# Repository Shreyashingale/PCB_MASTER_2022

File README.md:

# PCB_MASTER_2022
PCB files for robocon 2022

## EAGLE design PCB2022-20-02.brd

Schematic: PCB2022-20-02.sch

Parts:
3.3V_ARRAY: PINHD-1X5; 1X05
24V1, 24V2: AB_SCREW_TERMINAL_5MM_2PIN
BUZ-M: F/CM12P
BUZ-S: F/CM12P
C1, C2: C-EU025-025X050; C025-025X050
CYT-M: PINHD-1X3; 1X03
CYT-S: PINHD-1X3; 1X03
DEBUG-M: LED5MM
DEBUG-S: LED5MM
ENC-1, ENC-2: PINHD-1X4; 1X04
GNDARRAY: PINHD-1X5; 1X05
H2, H3, H4, H5, H6: MOUNT-HOLE3.2; 3,2
I2C-M1, I2C-M2, I2C-S1, I2C-S2: 4PIN_RELIMATE_CONNECTOR
LIM1, LIM2: AB_SCREW_TER_5MM_3PIN
LM358: DIL8; DIL08
M1, M2, M3, M5, M6: PINHD-1X8; 1X08
M4: PINHD-1X10; 1X10
M7: PINHD-2X18; 2X18
M-PL: D5-1A; SIL05A
M-SOLENOID1, M-SOLENOID2: AB_SCREW_TERMINAL_5MM_2PIN
M-SOLENOIDS: AB_SCREW_TER_5MM_3PIN
MASTER: ARDUINO_MEGA
NRF_SLAVE: PINHD-2X4; 2X04
ODRV-M1, ODRV-M2, ODRV-M3: 3PIN_RELIMATE_CONNECTOR
ODRV-S1, ODRV-S2, ODRV-S3: 3PIN_RELIMATE_CONNECTOR
P1, P2, P3, P4: AB_RIGHT_TER_BLK_3PIN
PARALLEL: SW_DIP-7; EDG-07
PPR-M: PINHD-1X3; 1X03
PPR-S: PINHD-1X3; 1X03
R1, R2, R3, R4: R-US_0204/5; 0204/5
RESET: DIP02YL
S1: PINHD-1X10; 1X10
S2, S3, S5, S6, S7: PINHD-1X8; 1X08
S4: PINHD-2X18; 2X18
S-CYT-PPR: 255SB
S-ENC-1, S-ENC-2: PINHD-1X4; 1X04
S-LIM1, S-LIM2: AB_SCREW_TER_5MM_3PIN
S-PL: D5-1A; SIL05A
S-SOLENOID1, S-SOLENOID2: AB_SCREW_TERMINAL_5MM_2PIN
S-SOLENOIDS: AB_SCREW_TER_5MM_3PIN
SABM1, SABM2, SABM3: PINHD-1X2; 1X02
SABS1, SABS2, SABS3: PINHD-1X2; 1X02
SERIAL: DIP02YL
SERVO-M: 3PIN_RELIMATE_CONNECTOR
SERVO-S: 3PIN_RELIMATE_CONNECTOR
SHIELD: ARDUINO_USB_HOST_SHIELD
SLAVE: ARDUINO_MEGA
STEPPER-M: PINHD-1X4; 1X04
STEPPER-S: PINHD-1X4; 1X04
U$2: AB_JUMPER_ONE_WAY
U$3: LM2596_BUCK_CONVERTER
U$10, U$11, U$12, U$13: AB_7805_FLAT
ULN-MASTER: DIL16
ULN-SLAVE: DIL16
VCC: AB_SCREW_TERMINAL_5MM_2PIN

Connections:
3V3A: 3.3V_ARRAY.1, 3.3V_ARRAY.2, 3.3V_ARRAY.3, 3.3V_ARRAY.4, 3.3V_ARRAY.5, M1.4, MASTER.3V3, SHIELD.3V3
5V3: SLAVE.5V3
5VA: ENC-1.1, ENC-2.1, I2C-M1.4, I2C-M2.4, M1.5, M7.1, M7.2, M-PL.1 (A), MASTER.5V, MASTER.5V1, MASTER.5V2, MASTER.5V3, SERVO-M.2, SHIELD.5V, SHIELD.5V1
A0: M2.1, MASTER.A0, SHIELD.A0
A1: M2.2, MASTER.A1, SHIELD.A1
A2: M2.3, MASTER.A2, SHIELD.A2
A3: M2.4, MASTER.A3, SHIELD.A3
A4: M2.5, MASTER.A4, SHIELD.A4
A5: M2.6, MASTER.A5, SHIELD.A5
A6: M2.7, MASTER.A6
A7: M2.8, MASTER.A7
A8: M3.1, MASTER.A8
A9: M3.2, MASTER.A9
A10: M3.3, MASTER.A10
A11: M3.4, MASTER.A11
A12: M3.5, MASTER.A12
A13: M3.6, MASTER.A13
A14: M3.7, MASTER.A14
A15: M3.8, MASTER.A15
AREF: M4.8, MASTER.AREF, SHIELD.AREF
CYT: CYT-S.2, S-CYT-PPR.1 (O)
D2: M5.6, MASTER.D2, R2.2, SHIELD.D2
D3: M5.5, MASTER.D3, SHIELD.D3
D4: M5.4, MASTER.D4, SHIELD.D4
D5: M5.3, MASTER.D5, SABM1.2, SHIELD.D5
D6: M5.2, MASTER.D6, SABM2.2, SHIELD.D6
D7: M5.1, MASTER.D7, SABM3.2, SHIELD.D7
D8: CYT-M.2, M4.1, MASTER.D8, SHIELD.D8
D9: M4.2, MASTER.D9, ODRV-M1.1, SHIELD.D9
D10: M4.3, MASTER.D10, SHIELD.D10, STEPPER-M.1
D11: M4.4, MASTER.D11, SHIELD.D11, STEPPER-M.2
D12: M4.5, MASTER.D12, SERVO-M.1, SHIELD.D12
D13: M4.6, MASTER.D13, ODRV-M1.2, SHIELD.D13
D22: ENC-1.3, M7.3, M-PL.4 (C4), MASTER.D22
D23: ENC-2.3, M7.4, M-PL.2 (C2), MASTER.D23
D24: M7.5, MASTER.D24
D25: M7.6, MASTER.D25
D26: CYT-M.3, M7.7, MASTER.D26
D27: M7.8, MASTER.D27
D28: M7.9, MASTER.D28, U$11.3 (VO)
D29: M7.10, MASTER.D29, U$10.3 (VO)
D30: M7.11, MASTER.D30, ULN-MASTER.7
D31: M7.12, MASTER.D31, ULN-MASTER.6
D32: M7.13, MASTER.D32, ULN-MASTER.5
D33: M7.14, MASTER.D33, ULN-MASTER.4
D34: M7.15, MASTER.D34, ULN-MASTER.3
D35: M7.16, MASTER.D35, ULN-MASTER.2
D36: M7.17, MASTER.D36, ULN-MASTER.1
D37: M7.18, MASTER.D37
D38: LIM1.1, M7.19, MASTER.D38
D39: LIM1.2, M7.20, MASTER.D39
D40: LIM2.1, M7.21, MASTER.D40
D41: LIM2.2, M7.22, MASTER.D41
D42: BUZ-M.+ (1), M7.23, MASTER.D42
D43: M7.24, MASTER.D43, PARALLEL.8
D44: M7.25, MASTER.D44, PARALLEL.9
D45: M7.26, MASTER.D45, PARALLEL.10
D46: M7.27, MASTER.D46, PARALLEL.11
D47: M7.28, MASTER.D47, PARALLEL.12
D48: M7.29, MASTER.D48, PARALLEL.13
D49: M7.30, MASTER.D49, PARALLEL.14
D50: M7.31, MASTER.D50
D51: M7.32, MASTER.D51
D52: M7.33, MASTER.D52, R4.2
D53: M7.34, MASTER.D53
GND: BUZ-M.- (2), BUZ-S.- (2), C1.2, C2.2, CYT-M.1, CYT-S.1, DEBUG-M.K (C), DEBUG-S.K (C), ENC-1.4, ENC-2.4, GNDARRAY.1, GNDARRAY.2, GNDARRAY.3, GNDARRAY.4, GNDARRAY.5, I2C-M1.3, I2C-M2.3, I2C-S1.3, I2C-S2.3, LIM1.3, LIM2.3, LM358.4, M1.6, M1.7, M4.7, M7.35, M7.36, MASTER.GD3, MASTER.GD4, MASTER.GND, MASTER.GND1, MASTER.GND2, MASTER.GND5, NRF_SLAVE.1, ODRV-M1.3, ODRV-M2.3, ODRV-M3.3, ODRV-S1.3, ODRV-S2.3, ODRV-S3.3, P1.1, P2.1, P3.1, P4.1, PPR-M.1, PPR-S.3, RESET.3, RESET.4, S1.7, S4.35, S4.36, S7.6, S7.7, S-ENC-1.4, S-ENC-2.4, S-LIM1.3, S-LIM2.3, SABM1.1, SABM2.1, SABM3.1, SABS1.1, SABS2.1, SABS3.1, SERVO-M.3, SERVO-S.3, SHIELD.GND, SHIELD.GND1 (GD), SHIELD.GND2, SHIELD.GND3, SLAVE.GD3, SLAVE.GD4, SLAVE.GND, SLAVE.GND1, SLAVE.GND2, SLAVE.GND5, STEPPER-M.3, STEPPER-M.4, STEPPER-S.3, STEPPER-S.4, U$2.2, U$3.IN-, U$3.OUT-, U$10.2 (GND), U$11.2 (GND), U$12.2 (GND), U$13.2 (GND), ULN-MASTER.8, ULN-SLAVE.8
GND-A: U$2.1, VCC.2
IRQ: NRF_SLAVE.8
M-V1: M-SOLENOID1.2, ULN-MASTER.16
M-V2: M-SOLENOID1.1, ULN-MASTER.15
M-V3: M-SOLENOID2.2, ULN-MASTER.14
M-V4: M-SOLENOID2.1, ULN-MASTER.13
M-V5: M-SOLENOIDS.3, ULN-MASTER.12
M-V6: M-SOLENOIDS.2, ULN-MASTER.11
M-V7: M-SOLENOIDS.1, ULN-MASTER.10
MISO: MASTER.MISO, SHIELD.MISO (MI)
MOSI: MASTER.MOSI, SHIELD.MOSI (MO)
unnamed: C1.1, LM358.3, R2.1
unnamed: DEBUG-S.A, R1.1
unnamed: C2.1, LM358.5, R3.2
unnamed: DEBUG-M.A, R4.1
unnamed: M1.1, MASTER.-
unnamed: S7.1, SLAVE.-
OUT-M: LM358.1, LM358.2, PPR-M.2
OUT-S: LM358.6, LM358.7, PPR-S.2
PPR: R3.1, S-CYT-PPR.3 (S)
PROX1: P1.2, U$10.1 (VIN)
PROX2: P2.2, U$11.1 (VIN)
PROX3: P3.2, U$13.1 (VIN)
PROX4: P4.2, U$12.1 (VIN)
RST: M1.3, MASTER.RST, MASTER.RST1, RESET.1, SHIELD.RST, SHIELD.RST1
RX0: M5.8, MASTER.RX0, SERIAL.2, SHIELD.RX0 (RX)
RX1: ENC-2.2, M6.6, M-PL.3 (C3), MASTER.RX1
RX2: M6.4, MASTER.RX2, ODRV-M2.1
RX3: M6.2, MASTER.RX3, ODRV-M3.1
S-3V3: NRF_SLAVE.2, S7.4, SLAVE.3V3
S-5V: S4.1, S4.2, S-ENC-1.1, S-ENC-2.1, S-PL.1 (A), SLAVE.5V1, SLAVE.5V2
S-5VA: I2C-S1.4, I2C-S2.4, S7.5, SERVO-S.2, SLAVE.5V
S-A0: S6.1, SLAVE.A0
S-A1: S6.2, SLAVE.A1
S-A2: S6.3, SLAVE.A2
S-A3: S6.4, SLAVE.A3
S-A4: S6.5, SLAVE.A4
S-A5: S6.6, SLAVE.A5
S-A6: S6.7, SLAVE.A6
S-A7: S6.8, SLAVE.A7
S-A8: S5.1, SLAVE.A8
S-A9: S5.2, SLAVE.A9
S-A10: S5.3, SLAVE.A10
S-A11: S5.4, SLAVE.A11
S-A12: S5.5, SLAVE.A12
S-A13: S5.6, SLAVE.A13
S-A14: S5.7, SLAVE.A14
S-A15: S5.8, SLAVE.A15
S-AREF: S1.8, SLAVE.AREF
S-D2: NRF_SLAVE.3, S2.3, SLAVE.D2
S-D3: NRF_SLAVE.5, S2.4, SLAVE.D3
S-D4: NRF_SLAVE.4, S2.5, SLAVE.D4
S-D5: S2.6, SABS1.2, SLAVE.D5
S-D6: S2.7, SABS2.2, SLAVE.D6
S-D7: S2.8, SABS3.2, SLAVE.D7
S-D8: S1.1, S-CYT-PPR.2, SLAVE.D8
S-D9: ODRV-S1.1, S1.2, SLAVE.D9
S-D10: S1.3, SLAVE.D10, STEPPER-S.1
S-D11: S1.4, SLAVE.D11, STEPPER-S.2
S-D12: S1.5, SERVO-S.1, SLAVE.D12
S-D13: ODRV-S1.2, S1.6, SLAVE.D13
S-D22: S4.3, S-ENC-1.3, S-PL.4 (C4), SLAVE.D22
S-D23: S4.4, S-ENC-2.3, S-PL.2 (C2), SLAVE.D23
S-D24: S4.5, SLAVE.D24
S-D25: S4.6, SLAVE.D25
S-D26: CYT-S.3, S4.7, SLAVE.D26
S-D27: S4.8, SLAVE.D27
S-D28: S4.9, SLAVE.D28, U$12.3 (VO)
S-D29: S4.10, SLAVE.D29, U$13.3 (VO)
S-D30: S4.11, SLAVE.D30, ULN-SLAVE.7
S-D31: S4.12, SLAVE.D31, ULN-SLAVE.6
S-D32: S4.13, SLAVE.D32, ULN-SLAVE.5
S-D33: S4.14, SLAVE.D33, ULN-SLAVE.4
S-D34: S4.15, SLAVE.D34, ULN-SLAVE.3
S-D35: S4.16, SLAVE.D35, ULN-SLAVE.2
S-D36: S4.17, SLAVE.D36, ULN-SLAVE.1
S-D37: S4.18, SLAVE.D37
S-D38: S4.19, S-LIM1.1, SLAVE.D38
S-D39: S4.20, S-LIM1.2, SLAVE.D39
S-D40: S4.21, S-LIM2.1, SLAVE.D40
S-D41: S4.22, S-LIM2.2, SLAVE.D41
S-D42: BUZ-S.+ (1), S4.23, SLAVE.D42
S-D43: PARALLEL.7, S4.24, SLAVE.D43
S-D44: PARALLEL.6, S4.25, SLAVE.D44
S-D45: PARALLEL.5, S4.26, SLAVE.D45
S-D46: PARALLEL.4, S4.27, SLAVE.D46
S-D47: PARALLEL.3, S4.28, SLAVE.D47
S-D48: PARALLEL.2, S4.29, SLAVE.D48
S-D49: PARALLEL.1, S4.30, SLAVE.D49
S-D50: NRF_SLAVE.6, S4.31, SLAVE.D50
S-D51: NRF_SLAVE.7, S4.32, SLAVE.D51
S-D52: R1.2, S4.33, SLAVE.D52
S-D53: S4.34, SLAVE.D53
S-MISO: SLAVE.MISO
S-MOSI: SLAVE.MOSI
S-RST: SLAVE.RST1
S-RX0: S2.1, SERIAL.4, SLAVE.RX0
S-RX1: S3.3, S-ENC-2.2, S-PL.3 (C3), SLAVE.RX1
S-RX2: ODRV-S2.1, S3.5, SLAVE.RX2
S-RX3: ODRV-S3.1, S3.7, SLAVE.RX3
S-SCK: SLAVE.SCK
S-SCL: I2C-S1.2, I2C-S2.2, S1.10, S3.1, SLAVE.SCL, SLAVE.SCLU
S-SDA: I2C-S1.1, I2C-S2.1, S1.9, S3.2, SLAVE.SDA, SLAVE.SDAU
S-TX0: S2.2, SERIAL.3, SLAVE.TX0
S-TX1: S3.4, S-ENC-1.2, S-PL.5 (C5), SLAVE.TX1
S-TX2: ODRV-S2.2, S3.6, SLAVE.TX2
S-TX3: ODRV-S3.2, S3.8, SLAVE.TX3
S-V1: S-SOLENOID1.2, ULN-SLAVE.16
S-V2: S-SOLENOID1.1, ULN-SLAVE.15
S-V3: S-SOLENOID2.2, ULN-SLAVE.14
S-V4: S-SOLENOID2.1, ULN-SLAVE.13
S-V5: S-SOLENOIDS.3, ULN-SLAVE.12
S-V6: S-SOLENOIDS.2, ULN-SLAVE.11
S-V7: S-SOLENOIDS.1, ULN-SLAVE.10
S-VREF: S7.2, SLAVE.IOREF
SCK: MASTER.SCK, SHIELD.SCK (SC)
SCL: I2C-M1.2, I2C-M2.2, M4.10, M6.8, MASTER.SCL, MASTER.SCLU, SHIELD.SCL
SDA: I2C-M1.1, I2C-M2.1, M4.9, M6.7, MASTER.SDA, MASTER.SDAU, SHIELD.SDA
SRST: RESET.2, S7.3, SLAVE.RST
TX0: M5.7, MASTER.TX0, SERIAL.1, SHIELD.TX0 (TX)
TX1: ENC-1.2, M6.5, M-PL.5 (C5), MASTER.TX1
TX2: M6.3, MASTER.TX2, ODRV-M2.2
TX3: M6.1, MASTER.TX3, ODRV-M3.2
VCC: 24V1.1, 24V1.2, 24V2.1, 24V2.2, LM358.8, P1.3, P2.3, P3.3, P4.3, PPR-M.3, PPR-S.1, U$3.IN+, ULN-MASTER.9, ULN-SLAVE.9, VCC.1
VIN: M1.8, MASTER.VIN, S7.8, SHIELD.VIN, SLAVE.VIN, U$3.OUT+
VREF: M1.2, MASTER.IOREF, SHIELD.VREF

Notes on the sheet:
ULN 2003 with Solenoid
MASTER
Slave
I2C MASTER
I2C SLAVE
PROXIMITY SENSOR
STEPPER
SABERTOOTH MASTER
SABERTOOTH SLAVE
SERVO SLAVE
SERVO MASTER
ODRIVE MASTER
ODRIVE SLAVE
LIMIT SWITCH MASTER
LIMIT SWITCH SLAVE
CYTRON MASTER
CYTRON SLAVE
SERIAL COMM
BUCK

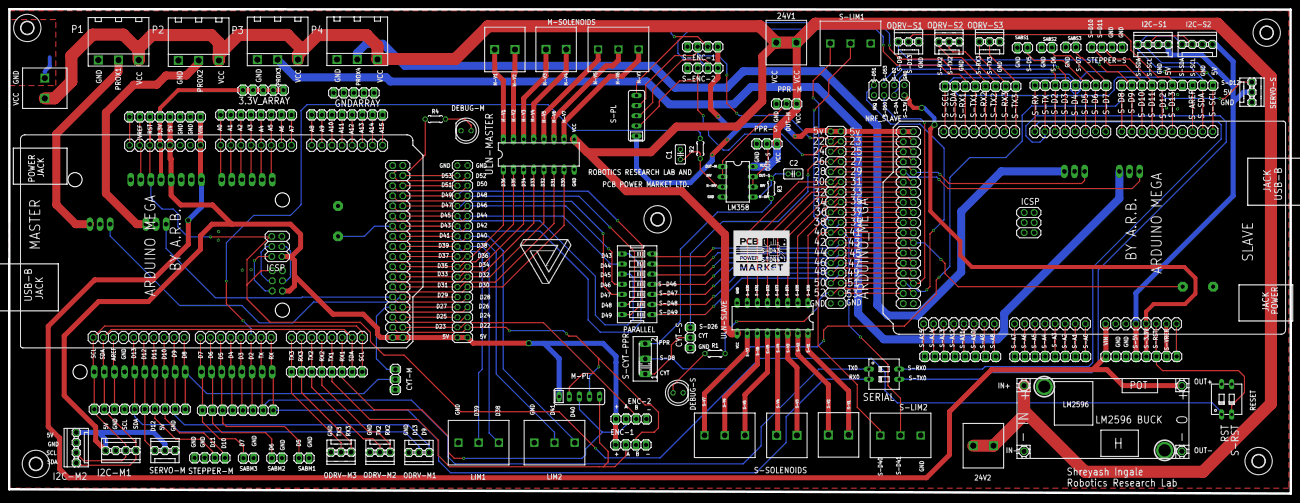
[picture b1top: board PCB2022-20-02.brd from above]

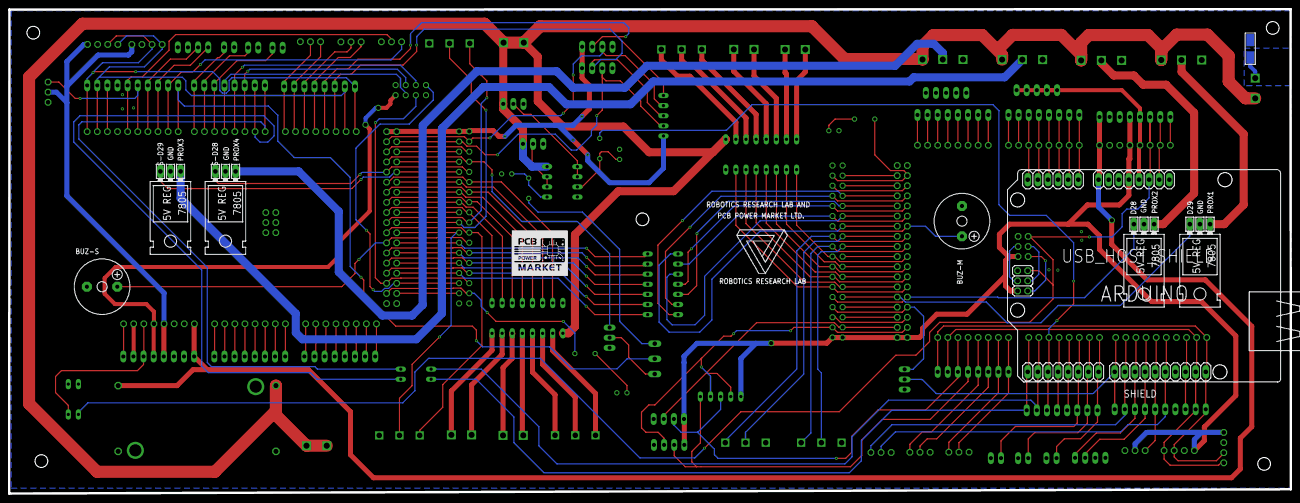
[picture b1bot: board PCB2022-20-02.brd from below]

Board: 2 copper layers, 321.8 x 121.6 mm, 95 parts (8 on the bottom side), 186 nets.

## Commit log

2022-04-03 pcb master
